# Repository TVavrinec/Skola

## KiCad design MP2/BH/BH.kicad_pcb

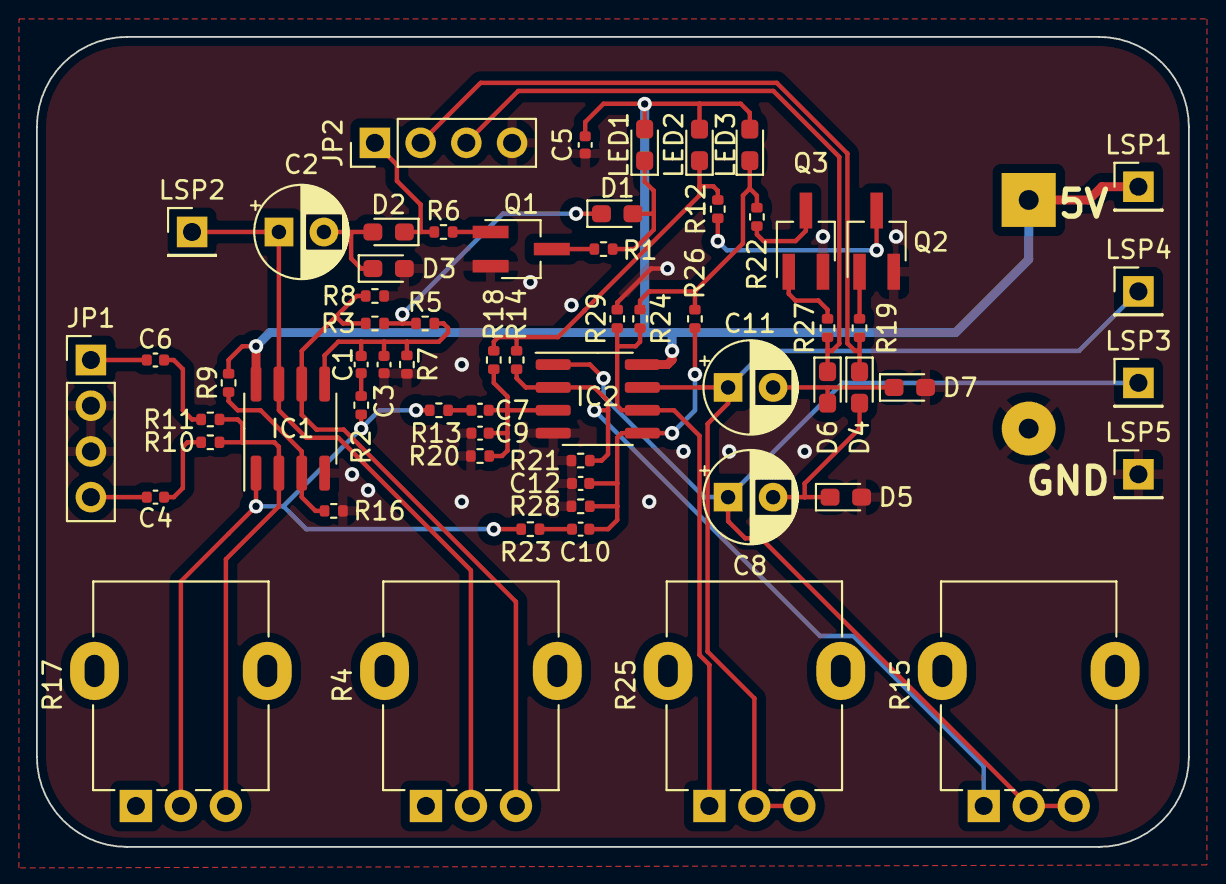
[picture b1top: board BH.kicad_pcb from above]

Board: 2 copper layers, 64.0 x 45.0 mm, 64 parts (1 on the bottom side), 37 nets.

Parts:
BT1: Battery; BatteryHolder_Keystone_2479_3xAAA
C1, C3, C5, C7, C9, C10, C12: C-EUC0402; C_0402_1005Metric
C2, C8, C11: 100u; CP_Radial_D5.0mm_P2.50mm
C4, C6: 2u2; C_0402_1005Metric
D1, D2, D3, D4, D5, D6, D7: 1N4148DO35-7; D_0603_1608Metric_Pad1.05x0.95mm_HandSolder
IC1, IC2: AD8599R; SOIC-8_3.9x4.9mm_P1.27mm
JP1, JP2: PINHD-1X4; PinHeader_1x04_P2.54mm_Vertical
LED1, LED2, LED3: LEDSML0603; D_0603_1608Metric_Pad1.05x0.95mm_HandSolder
LSP1, LSP2, LSP3, LSP4, LSP5: LSP10; PinHeader_1x01_P2.54mm_Vertical
Q1, Q2, Q3: BCF29SMD; SOT-23W_Handsoldering
R1, R2, R3, R5, R6, R7, R8, R9, R10, R11, R12, R13, R14, R16, R18, R19, R20, R21, R22, R23, R24, R26, R27, R28, R29: R-EU_R0402; R_0402_1005Metric
R4, R15, R17, R25: EVUL; Potentiometer_Alpha_RD901F-40-00D_Single_Vertical

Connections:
+5V: BT1.1 (+), C5.1, IC1.8 (V+), IC2.8 (V+), LED1.2 (A), LED2.2 (A), LED3.2 (A), LSP1.1 (MP), R9.2
GND: BT1.2 (-), C3.2, C5.2, C9.2, C12.2, D3.2 (A), D5.2 (A), D7.2 (A), IC1.4 (V-), IC2.4 (V-), JP1.2, JP1.3, JP2.4, LSP5.1 (MP), Q1.2 (E), Q2.2 (E), Q3.2 (E), R7.2, R8.2, R16.1, R20.2, R21.2, R28.2, R29.2
unnamed: C1.1, R2.1
unnamed: C1.2, C3.1, IC1.5 (IN+), R5.2, R7.1
unnamed: C2.1 (+), IC1.7 (OUT), LSP2.1 (MP), R4.2 (S)
unnamed: C2.2 (-), D2.2 (A), D3.1 (C)
unnamed: C7.1, R13.1
unnamed: C7.2, C9.1, IC2.3 (IN+), R18.2, R20.1
unnamed: C8.1 (+), IC2.1 (OUT), LSP3.1 (MP), R15.2 (S), R15.3 (E)
unnamed: C8.2 (-), D4.2 (A), D5.1 (C)
unnamed: C10.1, R23.1
unnamed: C10.2, C12.1, IC2.5 (IN+), R26.2, R28.1
unnamed: C11.1 (+), IC2.7 (OUT), LSP4.1 (MP), R25.2 (S), R25.3 (E)
unnamed: C11.2 (-), D6.2 (A), D7.1 (C)
unnamed: D1.1 (C), R3.1, R5.1
unnamed: D1.2 (A), LED1.1 (C), R1.1
unnamed: D2.1 (C), JP2.1, R6.1
unnamed: D4.1 (C), JP2.2, R19.1
unnamed: D6.1 (C), JP2.3, R27.1
unnamed: IC1.1 (OUT), R2.2, R13.2, R17.2 (S), R23.2
unnamed: IC1.2 (IN-), R10.2, R11.2, R17.3 (E)
unnamed: IC1.3 (IN+), R9.1, R16.2
unnamed: IC1.6 (IN-), R3.2, R4.3 (E), R8.1
unnamed: IC2.6 (IN-), R24.2, R25.1 (A), R29.1
unnamed: C6.1, JP1.1
unnamed: C4.2, JP1.4
unnamed: Q1.1 (B), R6.2
unnamed: Q1.3 (C), R1.2
unnamed: Q2.1 (B), R19.2
unnamed: Q2.3 (C), R12.2
unnamed: Q3.1 (B), R27.2
unnamed: Q3.3 (C), R22.2
unnamed: C4.1, R10.1
unnamed: C6.2, R11.1
unnamed: LED2.1 (C), R12.1, R14.1, R18.1
unnamed: IC2.2 (IN-), R14.2, R15.1 (A), R21.1
unnamed: LED3.1 (C), R22.1, R24.1, R26.1

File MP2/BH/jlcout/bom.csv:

Comment,Designator,Footprint,LCSC
Battery,BT1,BH:BatteryHolder_Keystone_2479_3xAAA,1
100n,"C1,C3,C5",Capacitor_SMD:C_0402_1005Metric,1
100u,"C2,C8,C11",Capacitor_THT:CP_Radial_D5.0mm_P2.50mm,1
2u2,"C4,C6",Capacitor_SMD:C_0402_1005Metric,1
10n,"C7,C9",Capacitor_SMD:C_0402_1005Metric,1
1n5,"C10,C12",Capacitor_SMD:C_0402_1005Metric,1
1N4148DO35-7,"D1,D2,D3,D4,D5,D6,D7",Diode_SMD:D_0603_1608Metric_Pad1.05x0.95mm_HandSolder,1
AD8599R,"IC1,IC2",Package_SO:SOIC-8_3.9x4.9mm_P1.27mm,1
PINHD-1X4,"JP1,JP2",Connector_PinHeader_2.54mm:PinHeader_1x04_P2.54mm_Vertical,1
LEDSML0603,"LED1,LED2,LED3",Diode_SMD:D_0603_1608Metric_Pad1.05x0.95mm_HandSolder,1
LSP10,"LSP1,LSP2,LSP3,LSP4,LSP5",Connector_PinHeader_2.54mm:PinHeader_1x01_P2.54mm_Vertical,1
BCF29SMD,"Q1,Q2,Q3",Package_TO_SOT_SMD:SOT-23W_Handsoldering,1
220,"R1,R12,R22",Resistor_SMD:R_0402_1005Metric,1
22k,"R2,R10,R11,R13,R23",Resistor_SMD:R_0402_1005Metric,1
47k,"R3,R5,R7,R8,R9,R14,R16,R18,R20,R21,R26,R28,R29",Resistor_SMD:R_0402_1005Metric,1
50k,"R4,R15,R17,R25",Potentiometer_THT:Potentiometer_Alpha_RD901F-40-00D_Single_Vertical,1
1k,"R6,R19,R24,R27",Resistor_SMD:R_0402_1005Metric,1

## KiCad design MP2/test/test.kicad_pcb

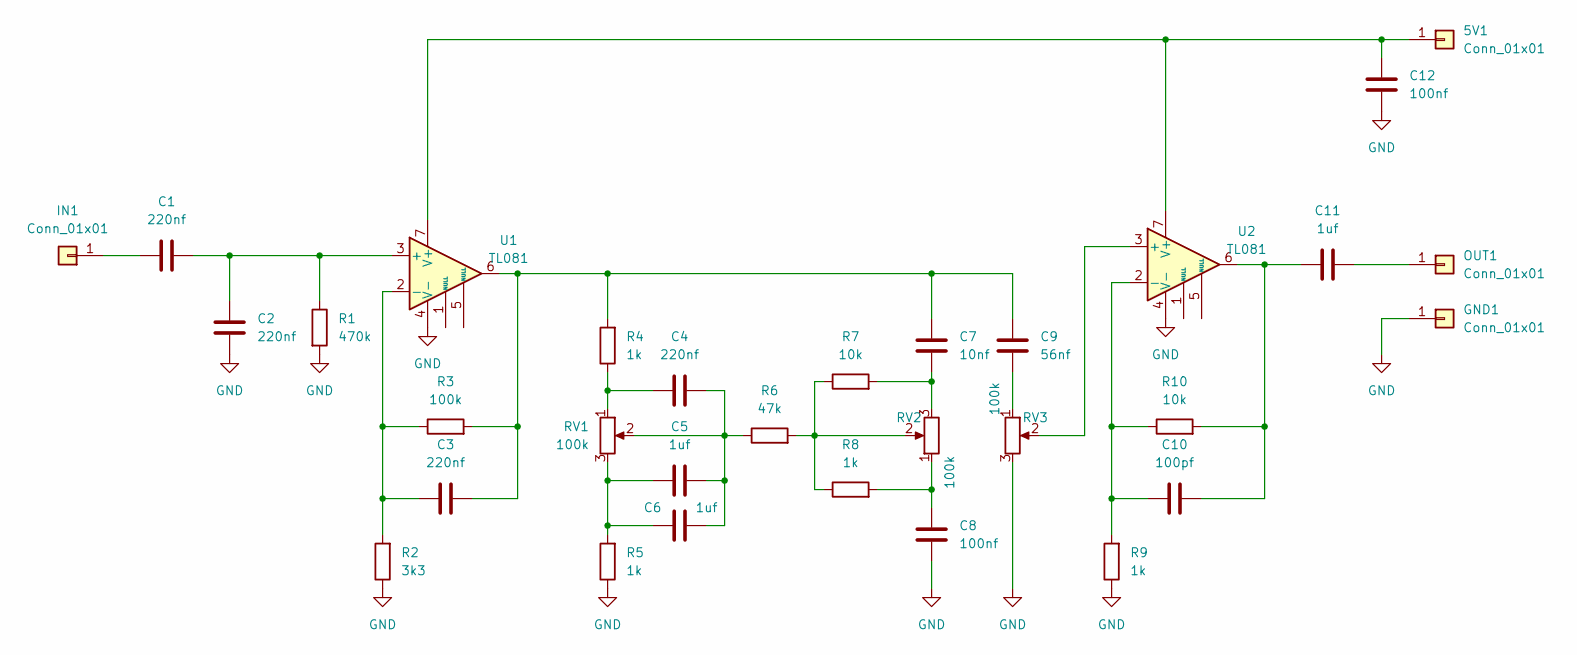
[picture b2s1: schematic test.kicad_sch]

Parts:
5V1: Conn_01x01; PinHeader_1x01_P2.54mm_Vertical
C1, C2, C3, C4: 220nf; C_0402_1005Metric
C5, C6, C11: 1uf; C_0402_1005Metric
C7: 10nf; C_0402_1005Metric
C8, C12: 100nf; C_0402_1005Metric
C9: 56nf; C_0402_1005Metric
C10: 100pf; C_0402_1005Metric
GND1: Conn_01x01; PinHeader_1x01_P2.54mm_Vertical
IN1: Conn_01x01; PinHeader_1x01_P2.54mm_Vertical
OUT1: Conn_01x01; PinHeader_1x01_P2.54mm_Vertical
R1: 470k; R_0402_1005Metric
R2: 3k3; R_0402_1005Metric
R3: 100k; R_0402_1005Metric
R4, R5, R8, R9: 1k; R_0402_1005Metric
R6: 47k; R_0402_1005Metric
R7, R10: 10k; R_0402_1005Metric
RV1, RV2, RV3: 100k; Potentiometer_ACP_CA9-V10_Vertical
U1, U2: TL081; SOIC-8-1EP_3.9x4.9mm_P1.27mm_EP2.29x3mm

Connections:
GND: C2.2, C8.1, C12.1, GND1.1, R1.2, R2.1, R5.1, R9.1, RV3.3, U1.4 (V-), U2.4 (V-)
unnamed: 5V1.1, C12.2, U1.7 (V+), U2.7 (V+)
unnamed: C1.2, C2.1, R1.1, U1.3 (+)
unnamed: C3.1, R2.2, R3.1, U1.2 (-)
unnamed: C3.2, C7.2, C9.2, R3.2, R4.2, U1.6
unnamed: C4.1, R4.1, RV1.1
unnamed: C4.2, C5.2, C6.2, R6.1, RV1.2
unnamed: C5.1, C6.1, R5.2, RV1.3
unnamed: C7.1, R7.2, RV2.3
unnamed: C9.1, RV3.1
unnamed: C10.1, R9.2, R10.1, U2.2 (-)
unnamed: C10.2, C11.1, R10.2, U2.6
unnamed: C1.1, IN1.1
unnamed: C11.2, OUT1.1
unnamed: R6.2, R7.1, R8.1, RV2.2
unnamed: C8.2, R8.2, RV2.1
unnamed: RV3.2, U2.3 (+)

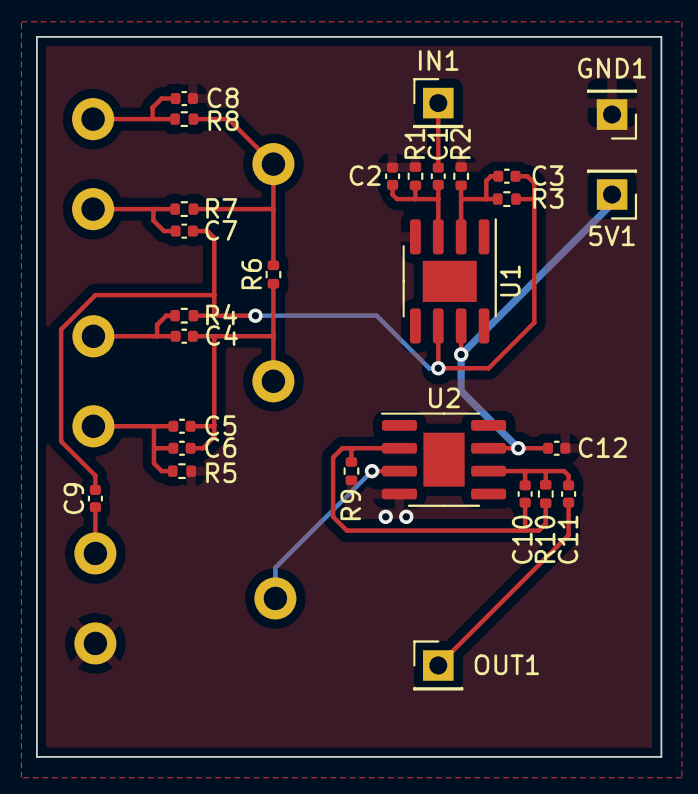
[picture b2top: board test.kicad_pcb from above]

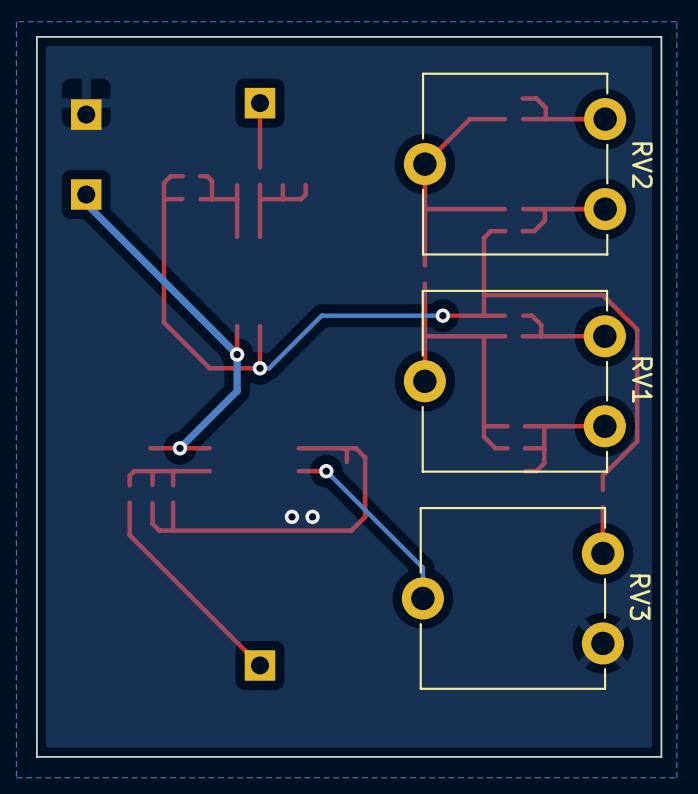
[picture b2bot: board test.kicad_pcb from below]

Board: 2 copper layers, 34.7 x 40.0 mm, 31 parts (3 on the bottom side), 17 nets.

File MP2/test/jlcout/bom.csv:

Comment,Designator,Footprint,LCSC
Conn_01x01,"5V1,GND1,IN1,OUT1",Connector_PinHeader_2.54mm:PinHeader_1x01_P2.54mm_Vertical,
220nf,"C1,C2,C3,C4",Capacitor_SMD:C_0402_1005Metric,
1uf,"C5,C6,C11",Capacitor_SMD:C_0402_1005Metric,
10nf,C7,Capacitor_SMD:C_0402_1005Metric,
100nf,"C8,C12",Capacitor_SMD:C_0402_1005Metric,
56nf,C9,Capacitor_SMD:C_0402_1005Metric,
100pf,C10,Capacitor_SMD:C_0402_1005Metric,
470k,R1,Resistor_SMD:R_0402_1005Metric,
3k3,R2,Resistor_SMD:R_0402_1005Metric,
100k,R3,Resistor_SMD:R_0402_1005Metric,
1k,"R4,R5,R8,R9",Resistor_SMD:R_0402_1005Metric,
47k,R6,Resistor_SMD:R_0402_1005Metric,
10k,"R7,R10",Resistor_SMD:R_0402_1005Metric,
100k,"RV1,RV2,RV3",Potentiometer_THT:Potentiometer_ACP_CA9-V10_Vertical,
TL081,"U1,U2",Package_SO:SOIC-8-1EP_3.9x4.9mm_P1.27mm_EP2.29x3mm,

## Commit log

2022-10-07 Inzenirska pedagogika
2022-10-07 PC2M
2022-10-08 AEY-ukol-1_vstupni_data
2022-10-08 AEY-vyhodnocovani
2022-10-08 MVE_lab2-zacatek_pripravy
2022-10-09 MVE_lab2_ukol-4
2022-10-09 MVE_lab2_zaver
2022-10-10 MVE-lab2_aproximace
2022-10-12 AEY_lab-pc1_prubehy-zkresleni
2022-10-13 AEY_lab-pc_final
2022-10-13 EMV_lab5_uvod
2022-10-14 EMV_lab5_opravy
2022-10-14 MVE_lab2_opravy
2022-10-29 bordel
2022-10-30 EMV_lab1 oprava názvů a inverze barev grafů
2022-10-30 gitignore
2022-11-03 EMV_lab1 hotovo
2022-11-09 AEY_lab3_priprava a PC cast
2022-11-09 AEY_lab3_asi hotovo
2022-11-10 AEY_lab3_go
2023-02-25 UZU_lab4_hotovo
2023-02-25 OZU_lab5_start
2024-02-28 lab-1
2024-02-28 .gitignore
2025-03-12 NAO extrakce parametru
2025-03-12 NAO proudová zrcadla
2025-04-28 Wip NAO
2025-05-05 NAO finák
